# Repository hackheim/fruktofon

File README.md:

# fruktofon

Det du trenger for å lage en fruktofon! :)

Arduino koden trenger arcore:   https://github.com/rkistner/arcore

og 

Arduino Bounce library:   http://playground.arduino.cc/Code/Bounce

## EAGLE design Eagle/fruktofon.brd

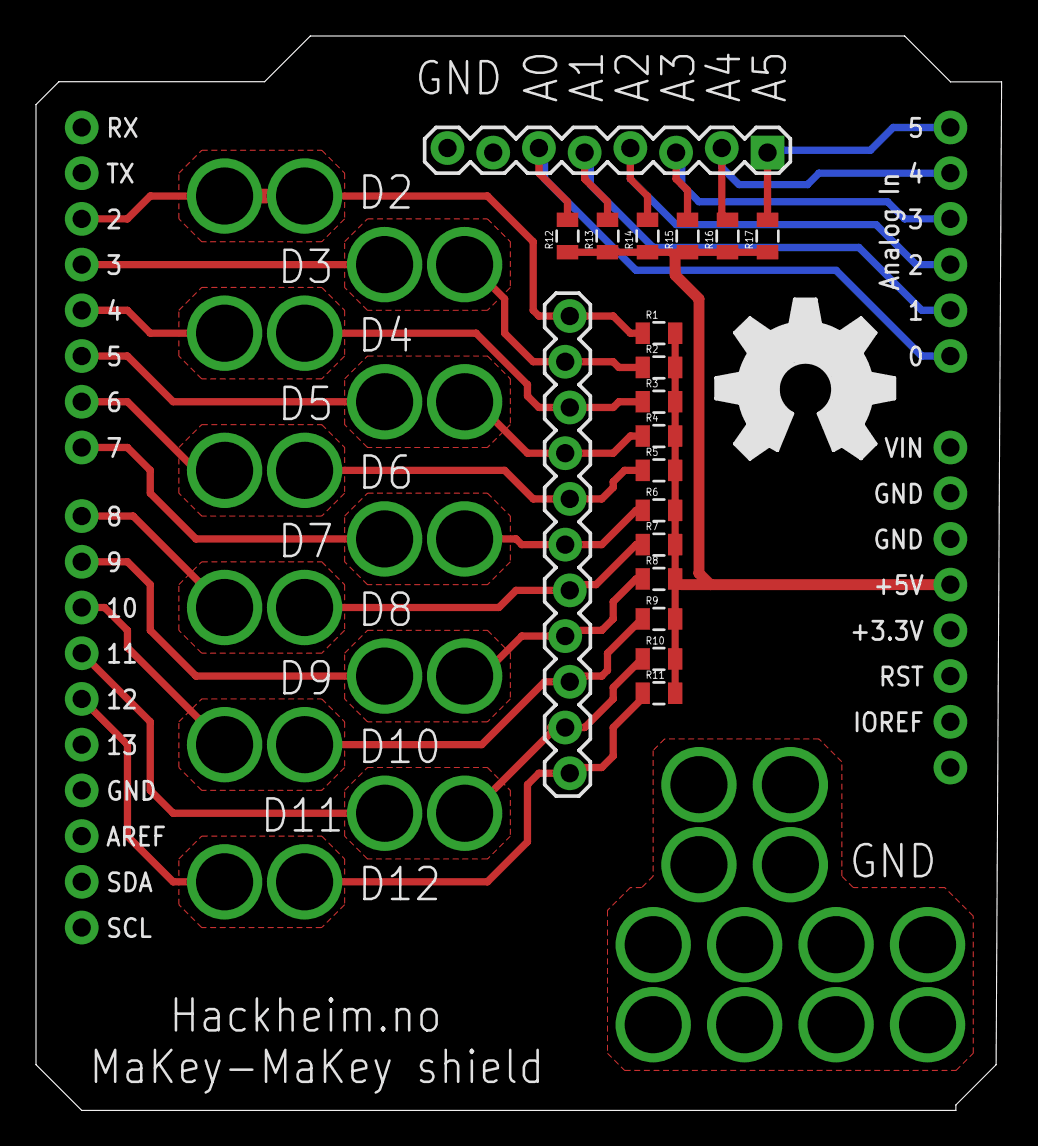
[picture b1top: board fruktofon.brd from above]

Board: 2 copper layers, 53.6 x 59.7 mm, 38 parts (0 on the bottom side), 19 nets.

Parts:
JP1: NA; 1X08_LOCK
JP2: M11LOCK; 1X11_LOCK
LOGO1: OSHW_LOGO_FILLX0350-NT; OSHW_FILLX350_NOTEXT
R1, R2, R3, R4, R5, R6, R7, R8, R9, R10, R11, R12, R13, R14, R15, R16, R17: 22M; 0805
U$1: ARDUINO_R3_SHIELD; UNO_R3_SHIELD
UP1, UP2, UP3, UP4, UP5, UP6, UP7, UP8, UP9, UP10, UP11, UP12, UP13, UP14, UP15, UP16, UP17: 1X01_ALLIGATOR_3MM

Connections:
+5V: R1.2, R2.2, R3.2, R4.2, R5.2, R6.2, R7.2, R8.2, R9.2, R10.2, R11.2, R12.1, R13.1, R14.1, R15.1, R16.1, R17.1, U$1.5V
D2: JP2.1, R1.1, U$1.D2, UP1.1@0, UP1.1@2
D3: JP2.2, R2.1, U$1.D3, UP2.1@0, UP2.1@2
D4: JP2.3, R3.1, U$1.D4, UP3.1@0, UP3.1@2
D5: JP2.4, R4.1, U$1.D5, UP4.1@0, UP4.1@2
D6: JP2.5, R5.1, U$1.D6, UP5.1@0, UP5.1@2
D7: JP2.6, R6.1, U$1.D7, UP6.1@0, UP6.1@2
D8: JP2.7, R7.1, U$1.D8, UP7.1@0, UP7.1@2
D9: JP2.8, R8.1, U$1.D9, UP8.1@0, UP8.1@2
D10: JP2.9, R9.1, U$1.D10, UP9.1@0, UP9.1@2
D11: JP2.10, R10.1, U$1.D11, UP10.1@0, UP10.1@2
D12: JP2.11, R11.1, U$1.D12, UP11.1@0, UP11.1@2
GND: JP1.7, JP1.8, U$1.GND@0, U$1.GND@1, U$1.GND@2, UP12.1@0, UP12.1@2, UP13.1@0, UP13.1@2, UP14.1@0, UP14.1@2, UP15.1@0, UP15.1@2, UP16.1@0, UP16.1@2, UP17.1@0, UP17.1@2
unnamed: JP1.6, R12.2, U$1.A0
unnamed: JP1.5, R13.2, U$1.A1
unnamed: JP1.4, R14.2, U$1.A2
unnamed: JP1.3, R15.2, U$1.A3
unnamed: JP1.2, R16.2, U$1.A4
unnamed: JP1.1, R17.2, U$1.A5

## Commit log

2015-08-26 Added MIT License
2015-08-26 Uploaded board, schema and Code

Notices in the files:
parts and their libraries:
SparkFun-Boards: Licensing: CC v3.0 Share-Alike You are welcome to use this library for commercial purposes.
